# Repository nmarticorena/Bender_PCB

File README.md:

## PCB de Bender 

### Recursos útiles

* [uchile robotics eagle lib](https://github.com/uchile-robotics/uchile_robotics_eagle_lib)
* [Adafruit Eagle library](https://github.com/adafruit/Adafruit-Eagle-Library)
* [SparkFun's Public Eagle PCB Footprints](https://github.com/sparkfun/SparkFun-Eagle-Libraries)

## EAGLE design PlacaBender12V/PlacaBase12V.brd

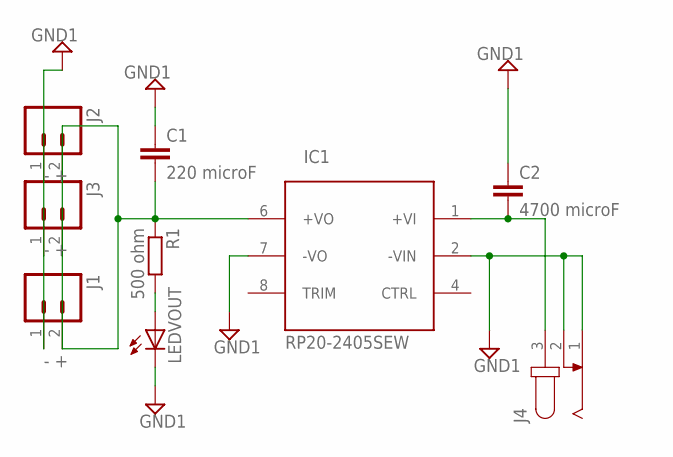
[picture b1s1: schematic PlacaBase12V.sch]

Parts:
C1: 220 microF; C025-040X050
C2: 4700 microF; C5B3.5
IC1: RP20-2405SEW; PACKAGE_RP20-2405SEW
J1, J2, J3: M02POLAR; MOLEX-1X2
J4: JACK-PLUG1; SPC4078
LEDVOUT: LED_ELD260; LED_LD260
R1: 500 ohm; 0207/5V

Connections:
GND1: C1.1, C2.1, IC1.2 (-VIN), IC1.7 (-VO), J1.1, J2.1, J3.1, J4.1, J4.2, LEDVOUT.K (C)
unnamed: LEDVOUT.A, R1.2
unnamed: C1.2, IC1.6 (+VO), J1.2, J2.2, J3.2, R1.1
unnamed: C2.2, IC1.1 (+VI), J4.3

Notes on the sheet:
- +

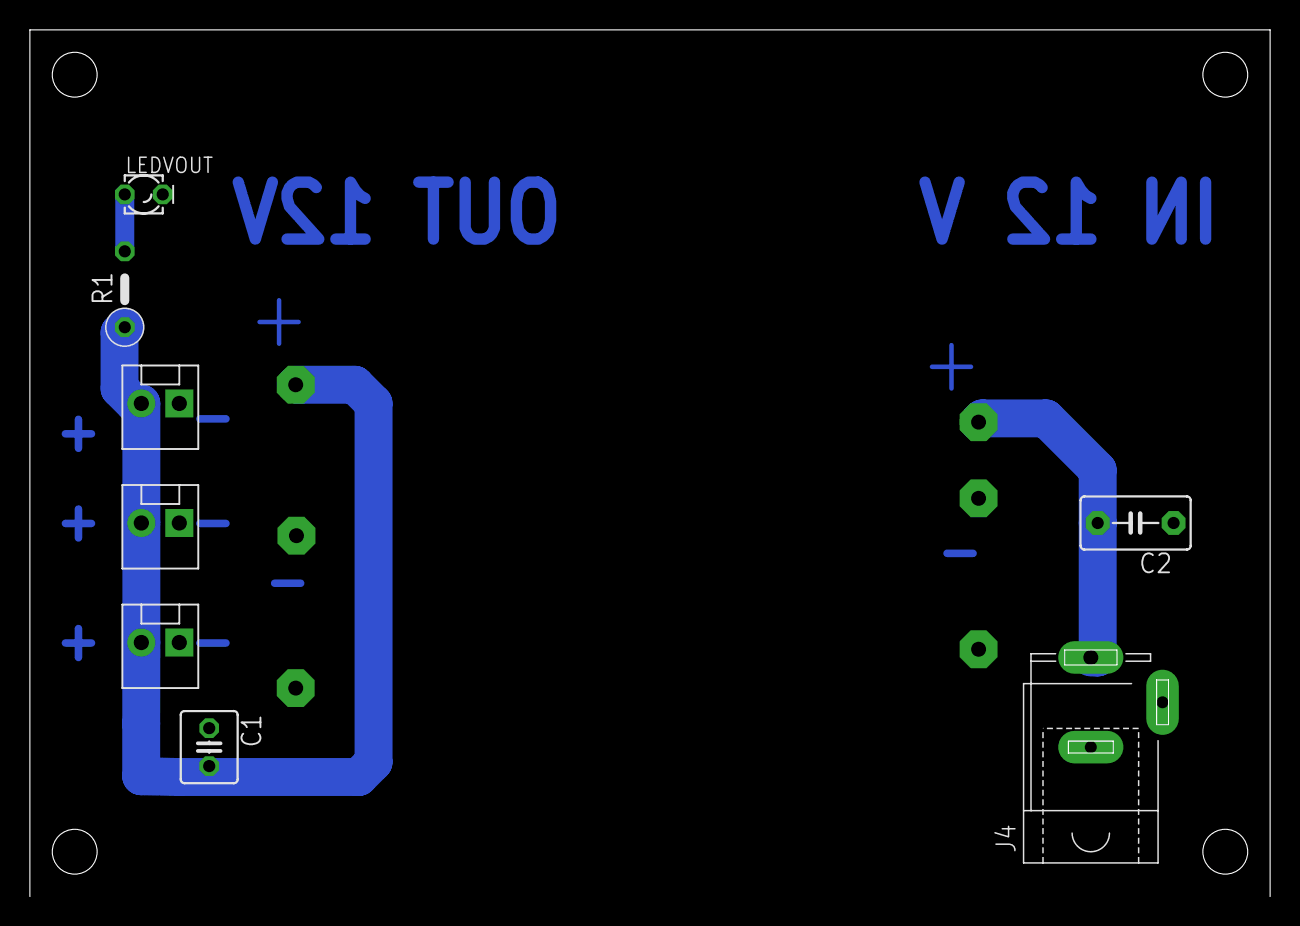
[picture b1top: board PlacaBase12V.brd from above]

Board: 2 copper layers, 83.0 x 58.0 mm, 9 parts (0 on the bottom side), 4 nets.

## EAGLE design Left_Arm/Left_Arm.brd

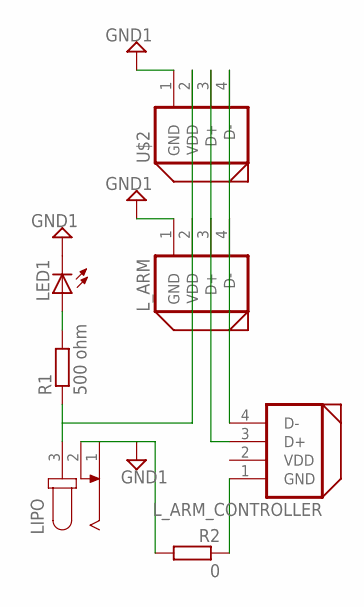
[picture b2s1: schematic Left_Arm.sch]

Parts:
LED1: LED_ELD260; LED_LD260
LIPO: JACK-PLUG1; SPC4078
L_ARM: DYNAMIXEL_RS485; DYNAMIXEL_SPOX_04
L_ARM_CONTROLLER: DYNAMIXEL_RS485; DYNAMIXEL_SPOX_04
R1: 500 ohm; 0207/10
R2: 0; M0805
U$2: DYNAMIXEL_RS485; DYNAMIXEL_SPOX_04

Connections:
GND1: LED1.K (C), LIPO.1, LIPO.2, L_ARM.1 (GND), R2.2, U$2.1 (GND)
unnamed: L_ARM.4 (D-), L_ARM_CONTROLLER.4 (D-), U$2.4 (D-)
unnamed: LED1.A, R1.2
unnamed: LIPO.3, L_ARM.2 (VDD), R1.1, U$2.2 (VDD)
unnamed: L_ARM.3 (D+), L_ARM_CONTROLLER.3 (D+), U$2.3 (D+)
unnamed: L_ARM_CONTROLLER.1 (GND), R2.1
VDD: L_ARM_CONTROLLER.2 (VDD)

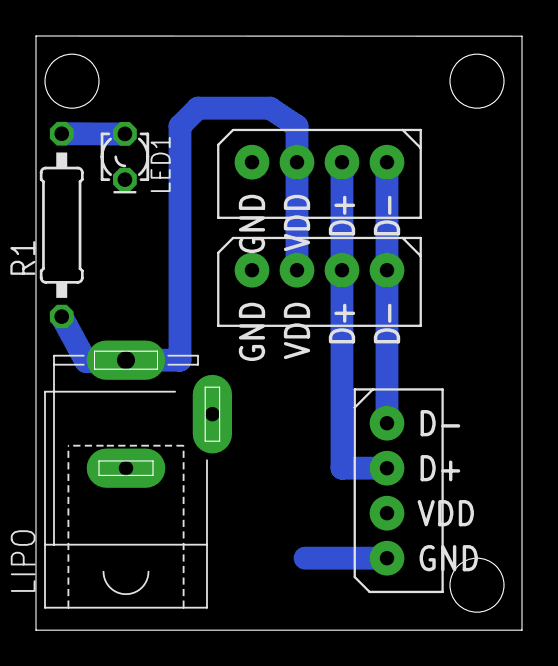
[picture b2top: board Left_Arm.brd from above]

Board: 2 copper layers, 27.0 x 33.0 mm, 7 parts (1 on the bottom side), 6 nets.

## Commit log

2017-01-25 add gitignore temporal eagle files
2017-01-25 Add Boards 12Volt
2017-01-25 Add Bender 12 volt out board
2017-01-25 update board 12 volt
2017-01-25 added proyect board 5 volt
2017-01-25 Fix errors
2017-01-25 New Readme
2017-01-25 fix readme
